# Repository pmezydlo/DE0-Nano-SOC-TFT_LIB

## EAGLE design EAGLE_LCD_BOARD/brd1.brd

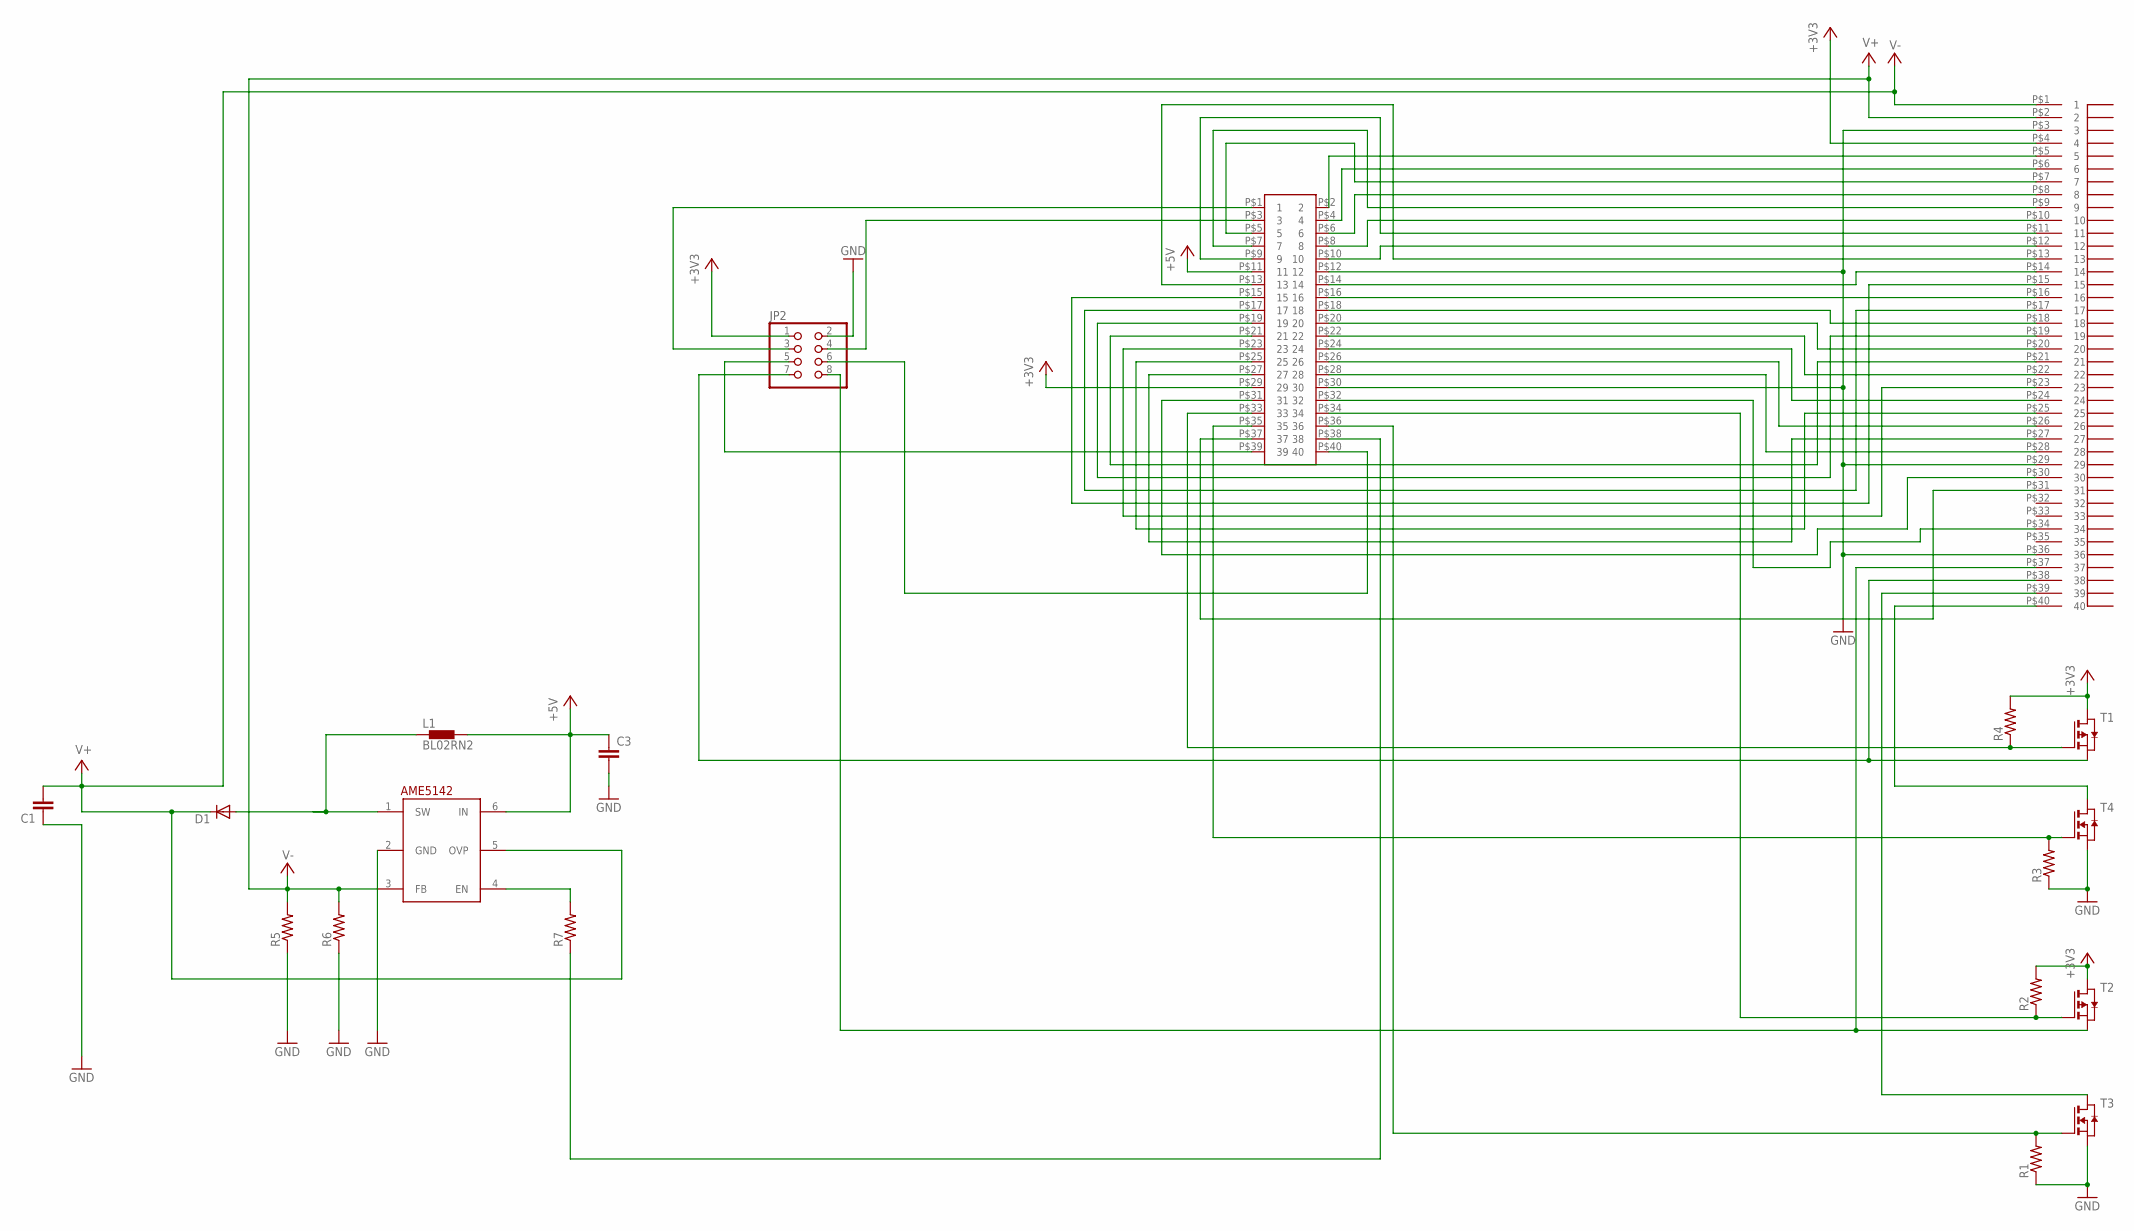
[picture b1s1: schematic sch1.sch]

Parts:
C1, C3: C-EUC0805; C0805
D1: DIODE-DO214AA; DO214AA
JP2: PINHD-2X4; 2X04
L1: BL02RN2
R1, R2, R3, R4, R5, R6, R7: R-US_R0805; R0805
T1, T2: PMOSSOT23; SOT-23
T3, T4: NMOSSOT23; SOT-23
U$1: DE0_40PIN_HEADER; HEADER20X2POL
U$2: AME
U$3: FPC_ZIF_PSP40; FPC_ZIF_40

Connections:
+3V3: JP2.1, R2.2, R4.2, T1.1 (D), T2.1 (D), U$1.P$29 (29), U$3.P$4 (4)
+5V: C3.1, L1.2, U$1.P$11 (11), U$2.6 (IN)
GND: C1.1, C3.2, JP2.2, R1.1, R3.1, R5.1, R6.1, T3.2 (S), T4.2 (S), U$1.P$12 (12), U$1.P$30 (30), U$2.2 (GND), U$3.P$3 (3), U$3.P$29 (29), U$3.P$36 (36)
unnamed: U$1.P$2 (2), U$3.P$5 (5)
unnamed: U$1.P$4 (4), U$3.P$6 (6)
unnamed: R2.1, T2.3 (G), U$1.P$34 (34)
unnamed: R3.2, T4.3 (G), U$1.P$35 (35)
unnamed: U$1.P$5 (5), U$3.P$7 (7)
unnamed: U$1.P$6 (6), U$3.P$8 (8)
unnamed: U$1.P$7 (7), U$3.P$9 (9)
unnamed: U$1.P$8 (8), U$3.P$10 (10)
unnamed: D1.A, L1.1, U$2.1 (SW)
unnamed: U$1.P$9 (9), U$3.P$11 (11)
unnamed: U$1.P$10 (10), U$3.P$12 (12)
unnamed: U$1.P$13 (13), U$3.P$13 (13)
unnamed: U$1.P$14 (14), U$3.P$14 (14)
unnamed: U$1.P$15 (15), U$3.P$15 (15)
unnamed: U$1.P$16 (16), U$3.P$16 (16)
unnamed: U$1.P$17 (17), U$3.P$17 (17)
unnamed: U$1.P$18 (18), U$3.P$18 (18)
unnamed: U$1.P$19 (19), U$3.P$19 (19)
unnamed: U$1.P$20 (20), U$3.P$20 (20)
unnamed: U$1.P$21 (21), U$3.P$21 (21)
unnamed: U$1.P$22 (22), U$3.P$22 (22)
unnamed: U$1.P$23 (23), U$3.P$23 (23)
unnamed: U$1.P$24 (24), U$3.P$24 (24)
unnamed: U$1.P$25 (25), U$3.P$25 (25)
unnamed: U$1.P$26 (26), U$3.P$26 (26)
unnamed: U$1.P$27 (27), U$3.P$27 (27)
unnamed: R7.2, U$2.4 (EN)
unnamed: U$1.P$28 (28), U$3.P$28 (28)
unnamed: U$1.P$31 (31), U$3.P$30 (30)
unnamed: U$1.P$32 (32), U$3.P$34 (34)
unnamed: JP2.8, T2.2 (S), U$3.P$37 (37)
unnamed: JP2.7, T1.2 (S), U$3.P$38 (38)
unnamed: T3.1 (D), U$3.P$39 (39)
unnamed: T4.1 (D), U$3.P$40 (40)
unnamed: JP2.3, U$1.P$1 (1)
unnamed: JP2.4, U$1.P$3 (3)
unnamed: R7.1, U$1.P$38 (38)
unnamed: U$1.P$37 (37), U$3.P$31 (31)
unnamed: R1.2, T3.3 (G), U$1.P$36 (36)
unnamed: JP2.5, U$1.P$39 (39)
unnamed: JP2.6, U$1.P$40 (40)
unnamed: R4.1, T1.3 (G), U$1.P$33 (33)
V+: C1.2, D1.C, U$2.5 (OVP), U$3.P$1 (1)
V-: R5.2, R6.2, U$2.3 (FB), U$3.P$2 (2)

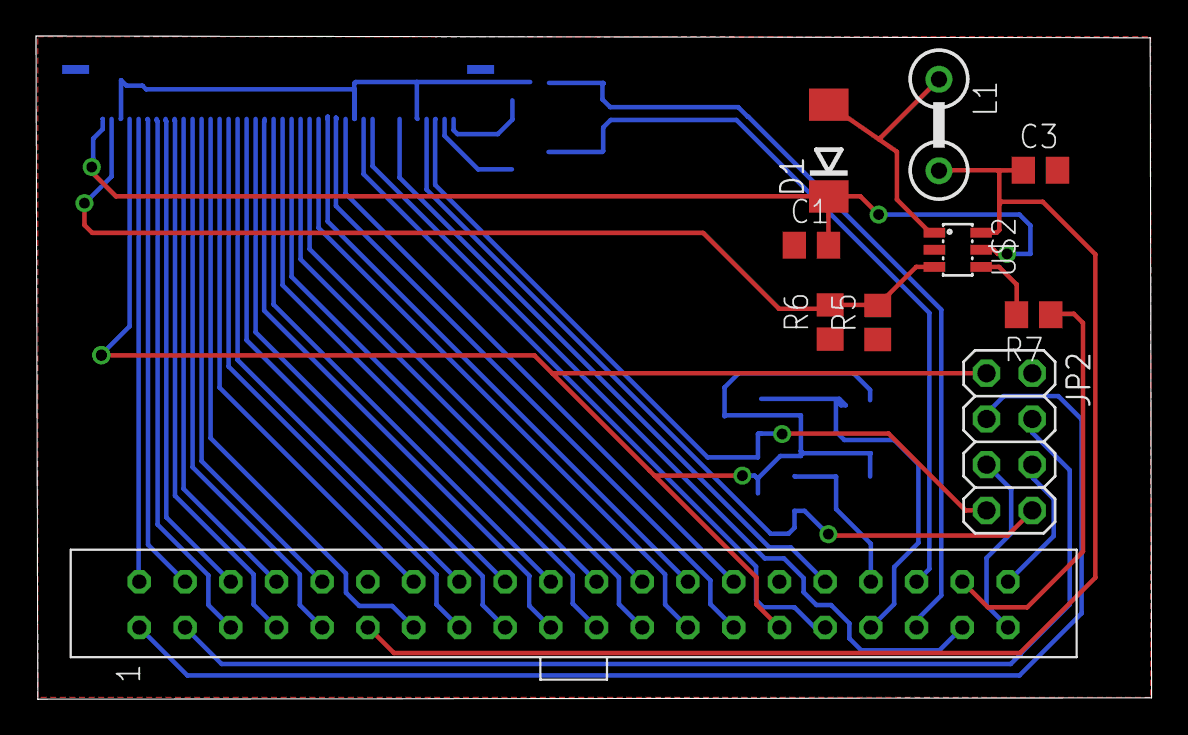
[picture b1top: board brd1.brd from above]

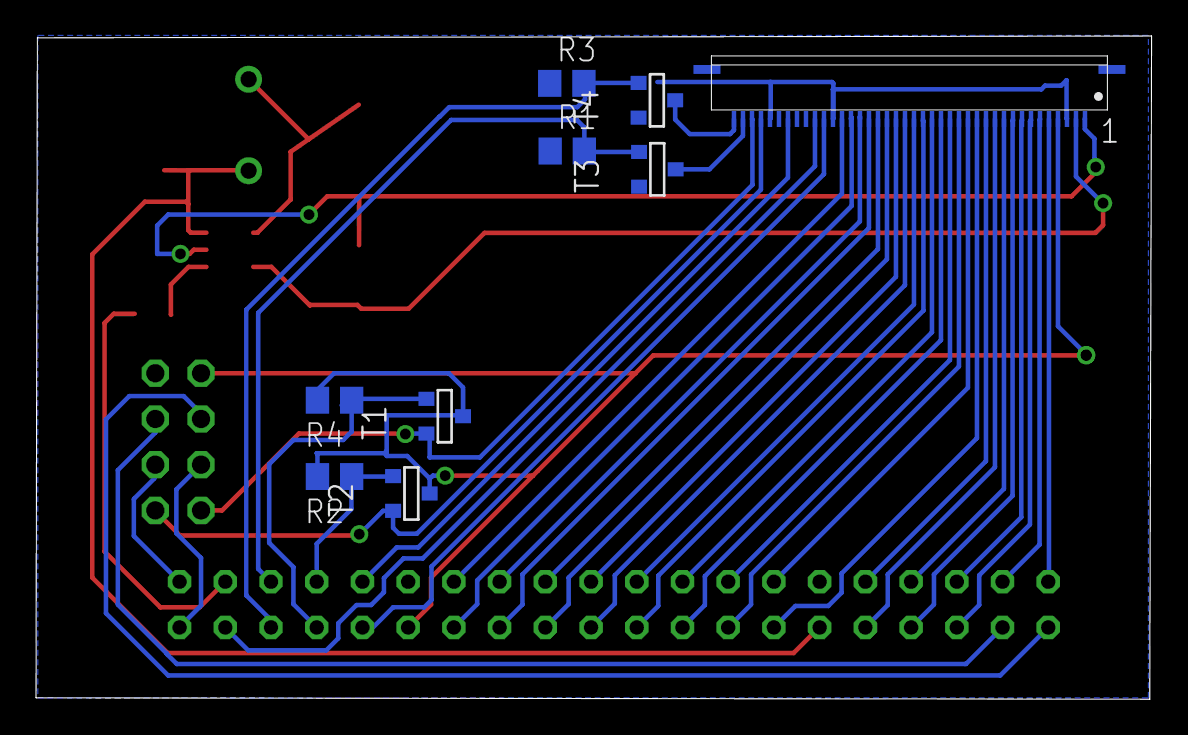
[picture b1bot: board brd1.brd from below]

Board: 2 copper layers, 62.0 x 36.8 mm, 19 parts (9 on the bottom side), 47 nets.
